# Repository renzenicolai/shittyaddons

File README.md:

# SAO storage

SAOs with an EEPROM chip

# Note about this branch

Based on the public domain version in the master branch.

The files in this branch including the logo are proprietary.

Copyright Renze Nicolai 2022

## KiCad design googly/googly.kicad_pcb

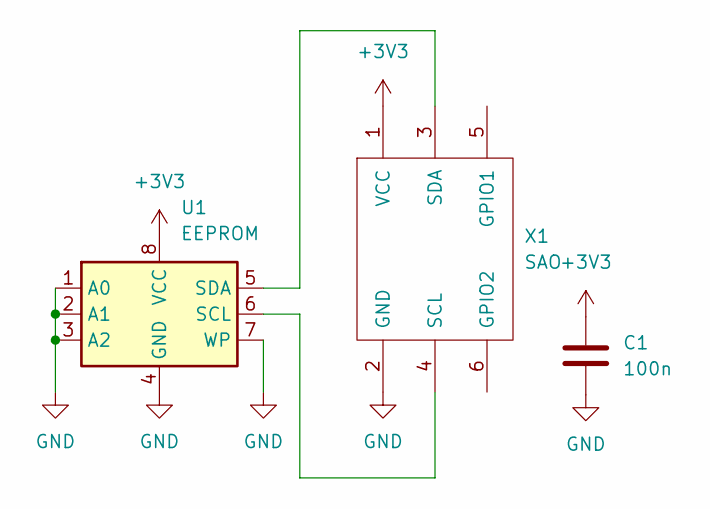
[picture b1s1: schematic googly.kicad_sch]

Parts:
C1: 100n; C_0603_1608Metric
U1: EEPROM; SOIC-8_3.9x4.9mm_P1.27mm
X1: SAO; PinHeader_2x03_P2.54mm_Vertical_SMD

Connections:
+3V3: C1.1, U1.8 (VCC), X1.1 (VCC)
GND: C1.2, U1.1 (A0), U1.2 (A1), U1.3 (A2), U1.4 (GND), U1.7 (WP), X1.2 (GND)
unnamed: U1.5 (SDA), X1.3 (SDA)
unnamed: U1.6 (SCL), X1.4 (SCL)

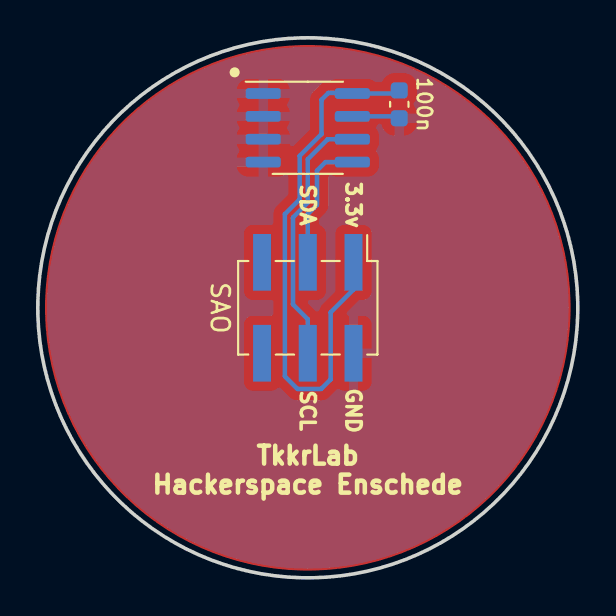
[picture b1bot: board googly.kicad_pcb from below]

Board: 2 copper layers, 30.0 x 30.0 mm, 3 parts (3 on the bottom side), 4 nets.

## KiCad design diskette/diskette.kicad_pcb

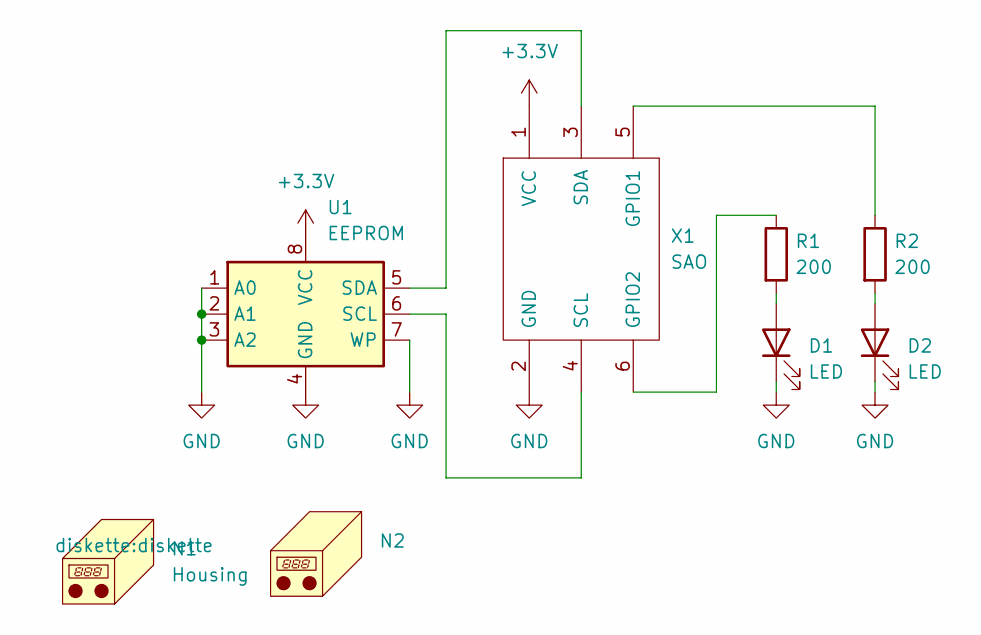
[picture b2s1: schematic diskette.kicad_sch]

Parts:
D1, D2: LED; LED_0805_2012Metric_Pad1.15x1.40mm_HandSolder
N1: Housing; diskette
N2: (no value)
R1, R2: 200; R_0805_2012Metric_Pad1.20x1.40mm_HandSolder
U1: EEPROM; SOIC-8_3.9x4.9mm_P1.27mm
X1: SAO; Badgelife-SAOv169-SAO-2x3

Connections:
+3V3: U1.8 (VCC), X1.1 (VCC)
GND: D1.1 (K), D2.1 (K), U1.1 (A0), U1.2 (A1), U1.3 (A2), U1.4 (GND), U1.7 (WP), X1.2 (GND)
unnamed: D1.2 (A), R1.2
unnamed: D2.2 (A), R2.2
unnamed: R1.1, X1.6 (GPIO2)
unnamed: R2.1, X1.5 (GPIO1)
unnamed: U1.5 (SDA), X1.3 (SDA)
unnamed: U1.6 (SCL), X1.4 (SCL)

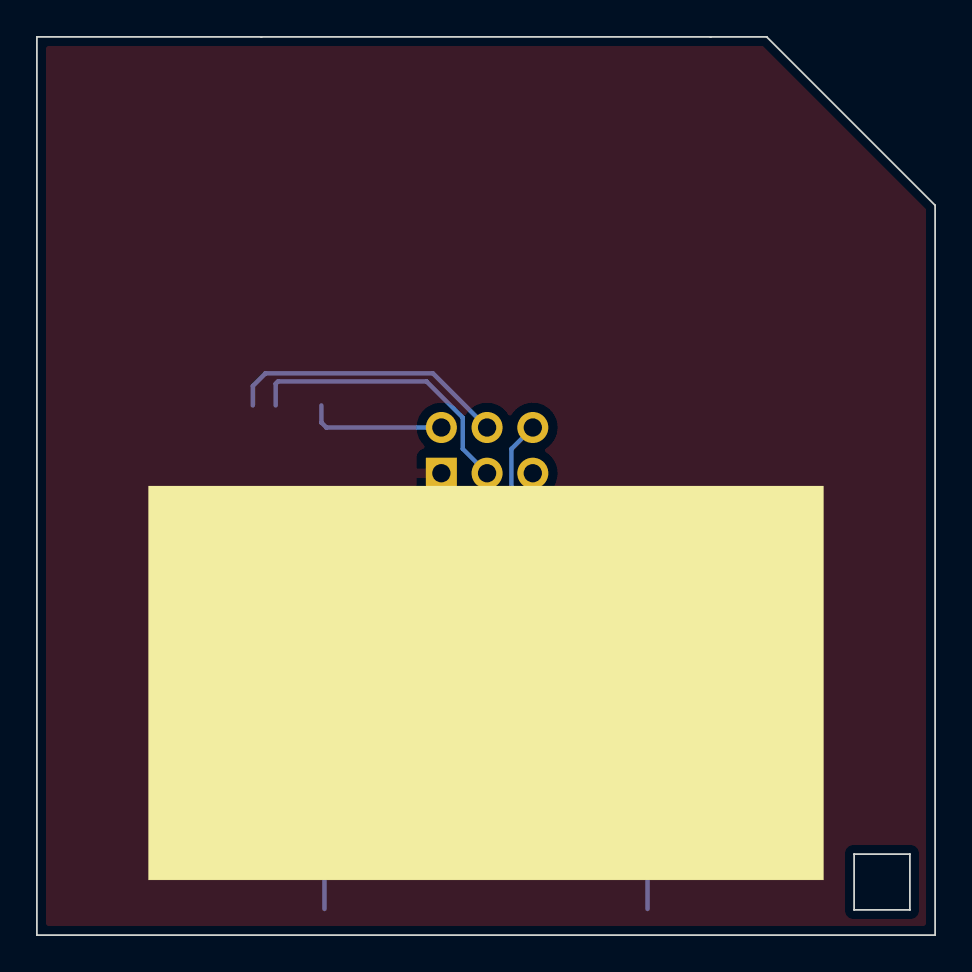
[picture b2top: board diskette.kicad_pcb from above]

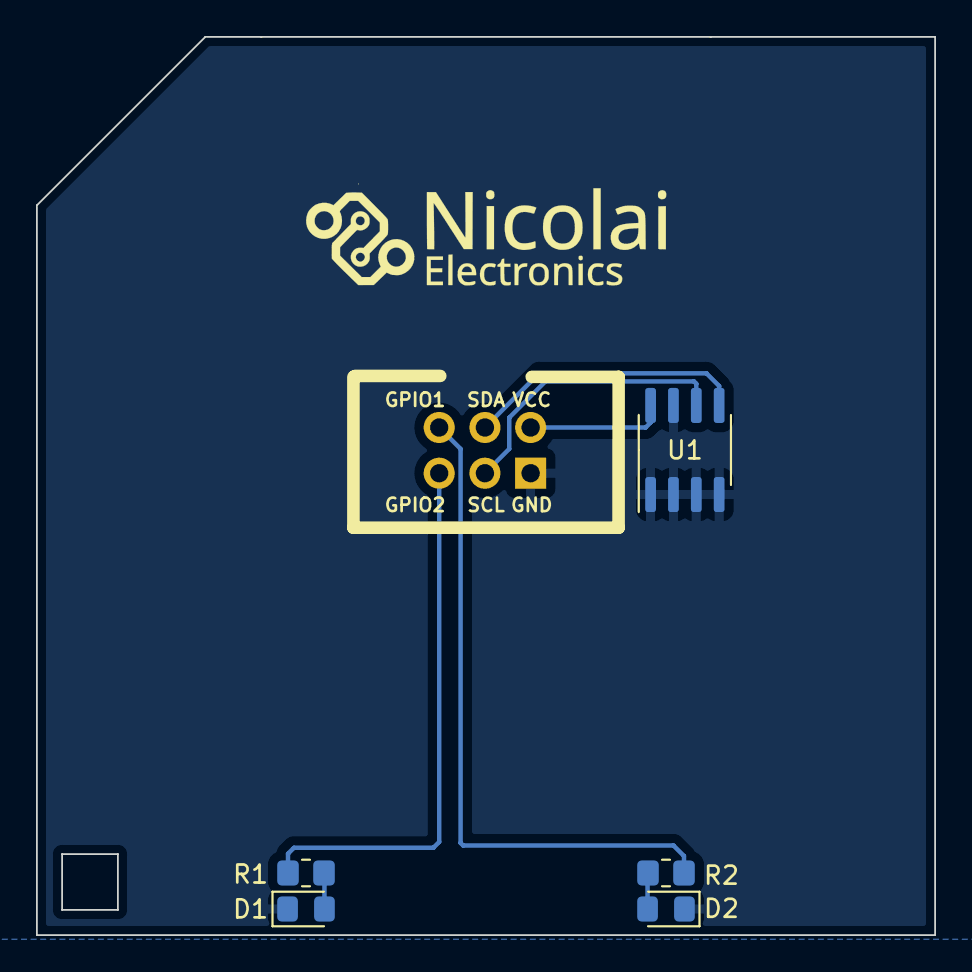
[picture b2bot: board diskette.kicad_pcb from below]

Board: 2 copper layers, 49.9 x 49.9 mm, 8 parts (6 on the bottom side), 8 nets.

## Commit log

2022-04-09 Add logo, add extra designs
2024-10-09 stuff
2024-10-11 Add googly eye sao
2024-10-12 Basic googly eye
